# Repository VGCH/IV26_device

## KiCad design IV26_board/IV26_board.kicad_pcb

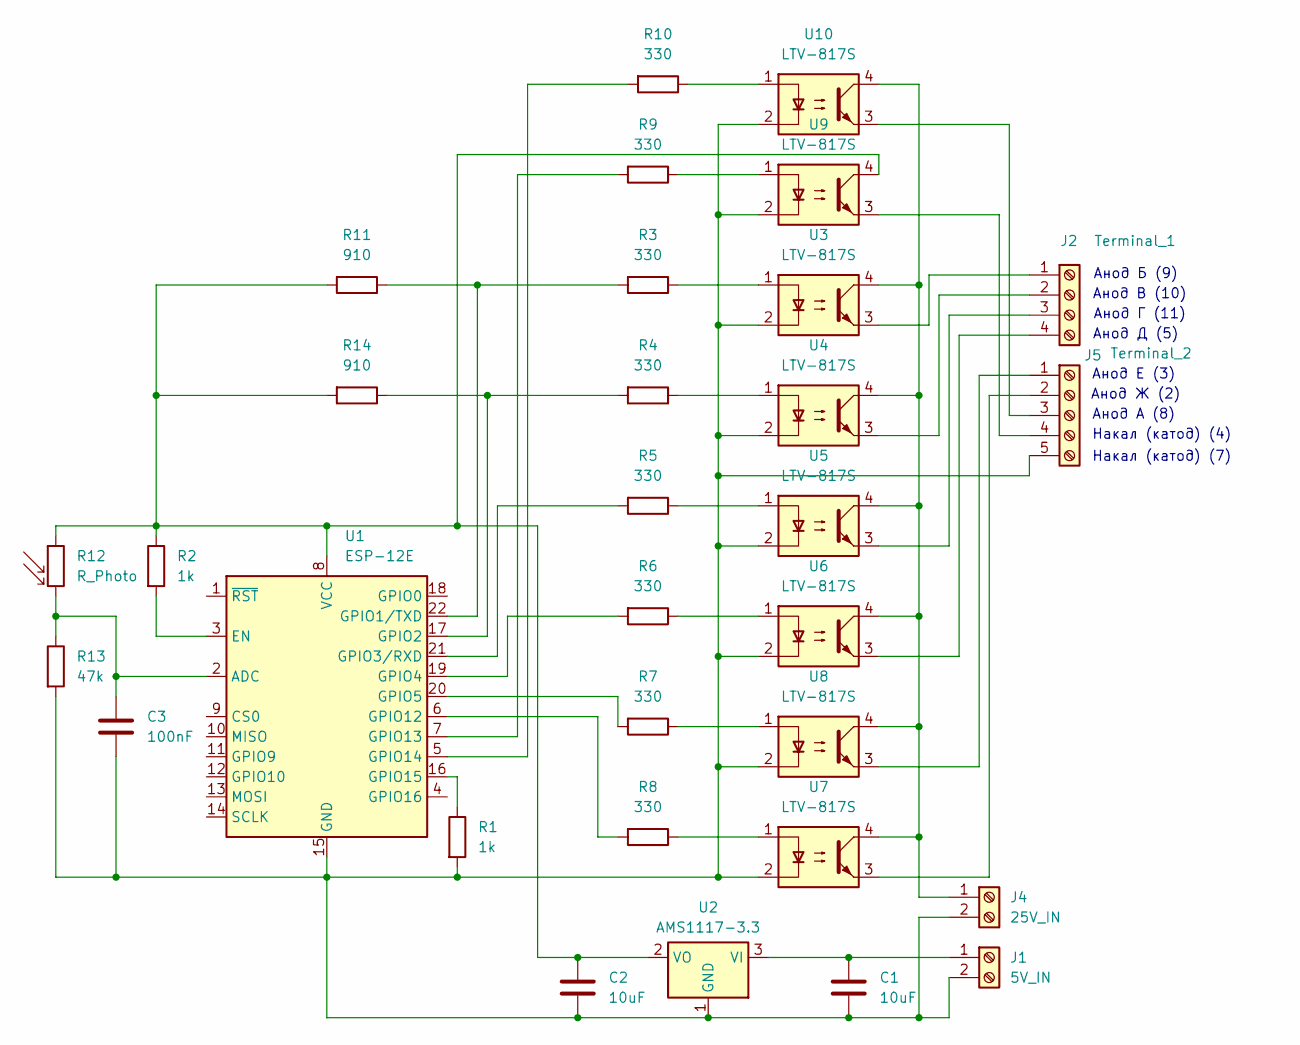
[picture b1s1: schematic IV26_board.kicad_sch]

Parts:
C1, C2: 10uF; C_0805_2012Metric
C3: 100nF; C_0805_2012Metric
J1: 5V_IN; TerminalBlock_MaiXu_MX126-5.0-02P_1x02_P5.00mm
J2: Terminal_1; TerminalBlock_MaiXu_MX126-5.0-04P_1x04_P5.00mm
J4: 25V_IN; TerminalBlock_MaiXu_MX126-5.0-02P_1x02_P5.00mm
J5: Terminal_2; TerminalBlock_MaiXu_MX126-5.0-05P_1x05_P5.00mm
R1, R2: 1k; R_0805_2012Metric
R3, R4, R5, R6, R7, R8, R9, R10: 330; R_0805_2012Metric
R11, R14: 910; R_0805_2012Metric
R12: R_Photo; R_LDR_5.1x4.3mm_P3.4mm_Vertical
R13: 47k; R_0805_2012Metric
U1: ESP-12E
U2: AMS1117-3.3; SOT-223-3_TabPin2
U3, U4, U5, U6, U7, U8, U9, U10: LTV-817S; SMDIP-4_W9.53mm

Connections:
unnamed: C1.1, J1.1, U2.3 (VI)
unnamed: C1.2, C2.2, C3.2, J1.2, J4.2, J5.5, R1.2, R13.2, U1.15 (GND), U2.1 (GND), U3.2, U4.2, U5.2, U6.2, U7.2, U8.2, U9.2, U10.2
unnamed: J2.1, U3.3
unnamed: J2.2, U4.3
unnamed: J2.3, U5.3
unnamed: J2.4, U6.3
unnamed: J4.1, U3.4, U4.4, U5.4, U6.4, U7.4, U8.4, U10.4
unnamed: J5.1, U8.3
unnamed: J5.2, U7.3
unnamed: J5.3, U10.3
unnamed: J5.4, U9.3
unnamed: R3.1, U3.1
unnamed: R4.1, U4.1
unnamed: R5.1, U5.1
unnamed: R6.1, U6.1
unnamed: R7.1, U8.1
unnamed: R8.1, U7.1
unnamed: R9.1, U9.1
unnamed: R10.1, U10.1
unnamed: C3.1, R12.2, R13.1, U1.2 (ADC)
unnamed: R2.2, U1.3 (EN)
unnamed: R3.2, R11.1, U1.22 (GPIO1/TXD)
unnamed: R4.2, R14.1, U1.17 (GPIO2)
unnamed: R5.2, U1.21 (GPIO3/RXD)
unnamed: R6.2, U1.19 (GPIO4)
unnamed: R7.2, U1.20 (GPIO5)
unnamed: R8.2, U1.6 (GPIO12)
unnamed: R9.2, U1.7 (GPIO13)
unnamed: R10.2, U1.5 (GPIO14)
unnamed: R1.1, U1.16 (GPIO15)
unnamed: C2.1, R2.1, R11.2, R12.1, R14.2, U1.8 (VCC), U2.2 (VO), U9.4

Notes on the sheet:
Анод А (8)
Анод Г (11)
Анод Б (9)
Анод В (10)
Анод Д (5)
Накал (катод) (7)
Анод Ж (2)
Накал (катод) (4)
Анод Е (3)

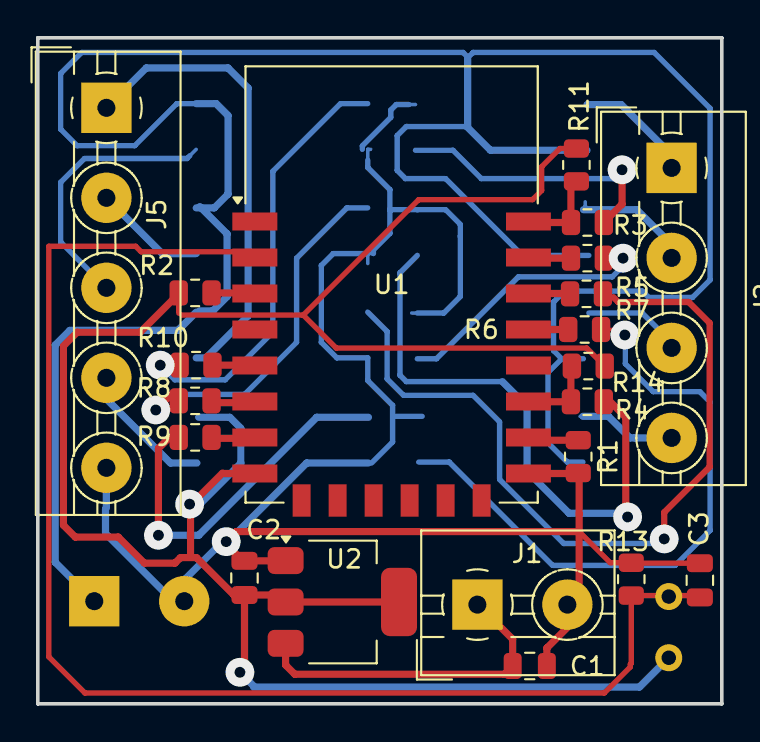
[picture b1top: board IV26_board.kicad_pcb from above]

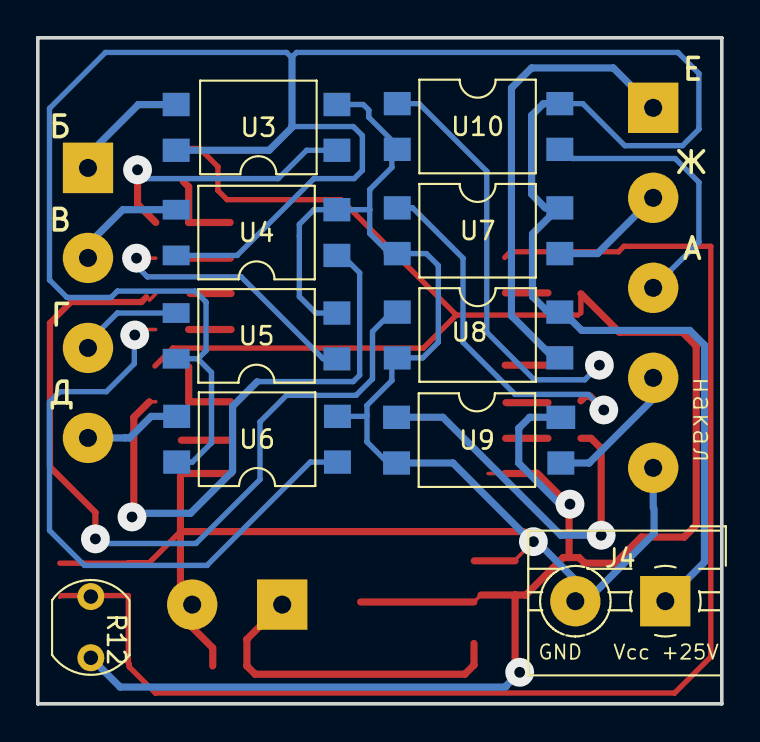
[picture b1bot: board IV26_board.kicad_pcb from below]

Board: 2 copper layers, 38.0 x 37.0 mm, 31 parts (10 on the bottom side), 31 nets.
